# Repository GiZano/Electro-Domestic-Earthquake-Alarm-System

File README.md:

<div align="center">

# 🌋 QuakeGuard
### Distributed Earthquake Early Warning System

**Full-Stack IoT Architecture for Real-Time Earthquake Detection**

> 📚 **Technical Specification:** A comprehensive architecture whitepaper is available in the `docs/` directory, compiled via Typst. For a browsable, topic-by-topic reference, check out the [project Wiki](https://github.com/GiZano/QuakeGuard/wiki).

</div>

---

🌐 **[Landing Page](https://giovanni-zanotti.is-a.dev/projects/quakeguard.html)** · 📚 **[Wiki](https://github.com/GiZano/QuakeGuard/wiki)** · 📄 **[Whitepaper (PDF)](docs/whitepaper/)** · 🗺️ **[ROADMAP](ROADMAP.md)**

---

## 📖 Overview

**QuakeGuard** is a full-stack IoT architecture for real-time detection, analysis, and reporting of seismic events. The system transforms everyday household appliances — washing machines, TVs, refrigerators — into a distributed seismic sensor network, each node capable of detecting and reporting earthquake activity autonomously.

Intelligent edge sensors (ESP32-C3 + ADXL345) analyze vibrations locally using professional-grade algorithms and transmit cryptographically signed data to an asynchronous cloud backend. The backend is engineesred to handle the massive traffic spikes — the **Thundering Herd** effect — typical during widespread seismic events, ensuring reliable alarm delivery without bottlenecking. A React Native mobile app receives real-time haptic and visual alerts via WebSocket.

### QuakeGuard Proprietary Hardware

*The QuakeGuard v2.0 fully assembled PCB, featuring the ESP32-C3 SuperMini, the ADXL345 accelerometer, and the u-blox GNSS module. For a complete list of required components, refer to the [Bill of Materials (BOM)](https://github.com/GiZano/QuakeGuard/wiki/Bill-of-Materials) in the Wiki.*

---

## 🏗️ System Architecture

```
ESP32-C3 + ADXL345
       │
       │  MQTT (signed payload)
       ▼
MQTT Bridge ──► POST /readings/ ──► ECDSA Verification
                                              │
                                              ▼
                                        Redis Queue
                                              │
                                              ▼
                                     Background Worker ────►┌───────────┐
                                      │           │ (Queue)  │ AI Worker │
                                      ▼           ▼          │ (Ollama)  │
                               PostgreSQL    Redis Pub/Sub ◄─└─────┬─────┘
                               + PostGIS               │
                                                   ▼
                                            WebSocket Broadcast
                                                  │
                                                  ▼
                                        React Native Mobile App
                                        (Haptic + Visual Alert)
```

The project follows **Microservices** and **Event-Driven Design** principles across three fully independent layers.

---

## 📡 IoT Edge (`firmware/`)

| Feature | Detail |
|---------|--------|
| Hardware | ESP32-C3 SuperMini + ADXL345 Accelerometer |
| Sampling Rate | 100 Hz |
| Detection Algorithm | STA/LTA (Short Term / Long Term Average) |
| Signal Processing | Digital High-Pass Filter (HPF) to remove gravity |
| Data Structure | Statically allocated Ring Buffers (`RingBuffer<100>` STA, `RingBuffer<1000>` LTA) |
| Security | ECDSA NIST256p cryptographic signing on every payload |
| Transmission | MQTT publish to `quakeguard/telemetry` |
| Provisioning | Automated device handshake on first boot via `POST /devices/register` |
| Secret Injection | Compile-time `ENROLLMENT_TOKEN` via PlatformIO pre-script + `#error` fail-fast |

---

## ☁️ Backend (`backend/`)

| Feature | Detail |
|---------|--------|
| Framework | FastAPI (Python 3.11), fully async |
| Security | API Key auth, ECDSA signature verification, Anti-Replay (300s window) |
| Message Broker | Redis — decouples ingestion from processing |
| Rate Limiting | Fixed-window 50 req/s per IP via Redis |
| Alert Engine | ML-like magnitude proxy (`M = log10(PGA_calib) + b`), threshold M ≥ 4.5 |
| Deduplication | Redis TTL cooldown lock per zone (60s), prevents alert storms |
| Persistence | PostgreSQL + PostGIS with `recorded_at` timestamps |
| Zone Assignment | Automatic via PostGIS `ST_Contains` spatial query, ordered by `ST_Area` ascending |
| Zone Seeding | 8 pre-populated global macro-regions + "Unknown Region" fallback |
| Observability | `GET /health` — concurrent PostgreSQL + Redis ping |
| Secrets | Fail-fast `RuntimeError` on missing env vars at startup |
| MQTT Bridge | `mqtt_subscriber.py` — forwards MQTT payloads to the secure HTTP pipeline |
| Edge AI | Asynchronous emergency report generation via local Ollama (Llama 3.2) |

---

## 📱 Frontend (`mobile/`)

| Feature | Detail |
|---------|--------|
| Framework | React Native (Expo) with TypeScript |
| Navigation | Expo Router — 3-tab Bottom Navigator (Monitor, Sensors Map, Settings) |
| State Management | Zustand slices (`usePreferencesStore`, `useAlertStore`) |
| Server State | TanStack Query + Axios — caching, background refetch, retry |
| Real-Time | WebSocket context with exponential backoff reconnection |
| Alert Delivery | SOS haptic vibration pattern + OS push notification via `expo-notifications` |
| Alert History | In-session feed of last 10 critical events |
| AI Report Banner | Inline AI-generated emergency report (summary + recommendations) for the latest alert, with "Report unavailable" badge on failures |
| Offline Mode | Toggle silences WebSocket, halts all TanStack Query polling |
| Notifications | `notificationsEnabled` toggle gates haptics and push notifications |
| Safe Areas | `react-native-safe-area-context` — Dynamic Island and punch-hole compatible |

---

## 🔐 Security Model

Data integrity is paramount in an emergency system. Every telemetry packet is cryptographically secured end-to-end.

```
ESP32 signs payload with ECDSA NIST256p (SHA256)
         ↓
Backend verifies signature against registered public key
         ↓
Timestamp validated within 300-second window (Anti-Replay)
         ↓
API Key checked on every request (X-API-Key header)
         ↓
Payload accepted → Redis Queue
```

**Threat model coverage:**
- ✅ Man-in-the-Middle (MitM) — ECDSA signature verification
- ✅ Spoofing — public key registration + signature check
- ✅ Replay attacks — 300-second timestamp window
- ✅ Brute force — rate limiting 50 req/s per IP
- ✅ Unauthorized access — API Key + enrollment token fail-fast

---

## 🚀 Quick Start

### Prerequisites

- Docker Desktop & Docker Compose
- PlatformIO (VS Code Extension)
- Node.js 18+ & Expo Go (mobile)
- A mobile hotspot or shared WiFi network for ESP32 + backend connectivity

### 1. Configure Environment Variables

```bash
cd backend
cp .env.example .env
```

Edit `.env` and set the required secrets:

```env
# --- Application Secrets ---
IOT_API_KEY=your_secret_key
MOBILE_WS_TOKEN=your_ws_token
ENROLLMENT_TOKEN=your_enrollment_token

# --- Database ---
POSTGRES_DB=quakeguard_db
POSTGRES_USER=developer
POSTGRES_PASSWORD=your_db_password
API_PORT=8000

# --- Cloud MQTT (HiveMQ) ---
MQTT_BROKER=your-cluster-id.s1.eu.hivemq.cloud
MQTT_PORT=8883
MQTT_USERNAME=your_mqtt_username
MQTT_PASSWORD=your_mqtt_password

# --- AI Emergency Reports (hybrid Edge AI architecture) ---
AI_REPORT_ENABLED=true
OLLAMA_HOST=http://127.0.0.1:11434
OLLAMA_MODEL=llama3.2:1b
```

> ⚠️ The backend will refuse to start if any of these are missing — this is intentional fail-fast behavior.

> 💡 **Edge AI Architecture (v2.0.0):** To maximize hardware efficiency and avoid Docker's GPU passthrough overhead, QuakeGuard employs an industrial **Hybrid Edge AI** pattern (similar to NVIDIA Jetson or Tesla FSD architectures). The core AI inference engine (Ollama) runs bare-metal on the host Linux OS, while the application microservices run in Docker and communicate via `network_mode: "host"`.
> 
> **To enable on-premise AI reports:**
> 1. Install Ollama natively on your Linux host: `curl -fsSL https://ollama.com/install.sh | sh`
> 2. Pull the model natively: `ollama pull llama3.2:1b`
> 3. Start the Docker stack with the AI worker profile: `docker compose --profile ai up --build -d`
> 
> Reports are generated entirely on your machine: telemetry never leaves the host.

### 2. Launch the Backend Stack

```bash
cd backend
docker compose up --build -d
```

| Endpoint | URL |
|----------|-----|
| API | `http://localhost:8000` |
| Swagger UI | `http://localhost:8000/docs` |
| Health Check | `http://localhost:8000/health` |

### 3. Configure and Flash the IoT Firmware

```bash
cd firmware
cp esp32_config.env.example esp32_config.env
# Edit esp32_config.env with your network IP and ENROLLMENT_TOKEN
```

Flash via PlatformIO. On first boot the device will:
1. Open a WiFi captive portal (`QuakeGuard-Setup`)
2. Connect to your network
3. Automatically register with the backend and receive a `sensor_id`

> 💡 If the sensor registers with `latitude=0.0, longitude=0.0` it will be assigned to "Unknown Region". Hardcode your coordinates in `main.cpp` for correct zone assignment until GPS integration is complete.

### 4. Launch the Mobile App

```bash
cd mobile
npm install
```

Update `constants/config.ts` with your machine's local IP:

```typescript
export const API_BASE_URL = "http://YOUR_LOCAL_IP:8000";
```

Create `.env` in the mobile root:

```env
EXPO_PUBLIC_IOT_API_KEY=your_secret_key
EXPO_PUBLIC_MOBILE_WS_TOKEN=your_ws_token
```

```bash
npx expo start
```

Scan the QR code with Expo Go. Ensure your phone is on the **same WiFi network** as the backend machine.

---

## 🧪 Stress Test

Validates the full pipeline: ingestion → Redis → worker → PostGIS → WebSocket alerts.

```bash
cd backend
export API_URL="http://localhost:8000"
export NUM_SENSORS=150
export CONCURRENCY_LIMIT=50
python -m tests.stress_test
```

**Three phases:**

| Phase | What it tests |
|-------|--------------|
| 🔥 Phase 1 — Firehose | 150 concurrent sensors, rate limiter validation |
| ⚔️ Phase 2 — Security | Bad signature blocked (401), Replay attack blocked (403) |
| 🔍 Phase 3 — E2E | DB persistence verified via polling `GET /sensors/{id}/statistics` |

A successful run ends with `🏆 SYSTEM CERTIFIED`.

---

## 🎮 Demo Mode

Trigger a simulated earthquake instantly from Swagger UI without running the stress test:

```
POST /demo/trigger-earthquake
```

Default payload (works with empty `{}`):
```json
{
  "zone_id": 1,
  "magnitude": 7.5,
  "message": "Simulated Critical Event"
}
```

This publishes directly to the Redis `quake_alerts` channel, bypassing the IoT pipeline entirely and triggering the mobile app alert UI within milliseconds.

---

## 🗺️ Geographic Zones

The database is pre-seeded with 8 global macro-regions. Sensors are automatically assigned to the correct zone via PostGIS spatial query at registration time.

| Zone | Coverage |
|------|----------|
| Italy - North | Lombardy, Veneto, Piedmont |
| Italy - Center | Tuscany, Lazio, Umbria |
| Italy - South & Islands | Campania, Sicily, Sardinia |
| Western Europe | France, Spain, Germany, UK |
| North America | USA, Canada, Mexico |
| South America | Brazil, Argentina, Chile |
| East Asia | China, Japan, India |
| Unknown Region | Fallback for unmapped coordinates |

---

## 🔄 CI/CD Pipeline

| Workflow | Trigger | Checks |
|----------|---------|--------|
| `backend-ci.yml` | `backend/**` | Bandit, Safety, stress test |
| `frontend-ci.yml` | `mobile/**` | ESLint, npm audit |
| `iot-ci.yml` | `firmware/**` | PlatformIO compilation |
| `pr-lint.yml` | All PRs | Semantic PR title (`type(scope): message`) |
| `devops-ci.yml` | `.github/workflows/**` | Actionlint workflow validation |

---

## 🗂️ Project Structure

```
QuakeGuard/
├── backend/
│   ├── src/
│   │   ├── main.py              # FastAPI gateway + REST endpoints
│   │   ├── security.py          # ECDSA, API Key, Anti-Replay
│   │   ├── worker.py            # Redis consumer + magnitude + alert engine + AI enqueue
│   │   ├── ai_report_worker.py  # Dedicated AI report consumer (Ollama + state machine)
│   │   ├── ollama_client.py     # Deterministic LLM client (anti-hallucination)
│   │   ├── mqtt_subscriber.py   # MQTT to HTTP bridge
│   │   ├── seed.py              # Geographic zone seeder
│   │   ├── models.py            # SQLAlchemy ORM models (+ EmergencyReport)
│   │   ├── schemas.py           # Pydantic request/response schemas
│   │   └── database.py          # DB engine and session factory
│   ├── tests/
│   │   ├── stress_test.py       # Critical E2E stress test suite
│   │   └── unit/                # Unit tests (worker, ollama client, AI worker, models, ...)
│   ├── init-scripts/
│   │   └── ollama-entrypoint.sh # Auto-pulls the Ollama model on startup
│   ├── build.ps1                # Automatic container publish
│   ├── docker-compose.yml
│   ├── Dockerfile
│   ├── mosquitto.conf
│   ├── requirements.txt         # Python requirements for backend development
│   └── .env.example
├── mobile/
│   ├── app/                         # Expo Router screens
│   │   └── (tabs)/
│   │       ├── index.tsx            # Monitor / Dashboard
│   │       ├── map.tsx              # Sensor Network Map
│   │       └── settings.tsx         # User Preferences
│   ├── api/                         # Axios client + TanStack Query hooks
│   ├── components/                  # Shared UI components
│   ├── store/                       # Zustand state slices
│   ├── context/
│   │   └── WebSocketContext.tsx     # Real-time alert context
│   └── constants/
│       └── config.ts                # Centralized configuration
├── firmware/
│   ├── src/
│   │   ├── main.cpp             # FreeRTOS tasks, STA/LTA, MQTT, provisioning
│   │   ├── DetectionCore.h      # Pure-C++ STA/LTA core (shared firmware/host, R1)
│   │   └── RingBuffer.h         # Statically allocated circular buffer
│   ├── tools/
│   │   └── detect_cli.cpp       # Native host CLI (SIL replay, same core)
│   ├── test/                    # Test scripts to insert into the ESP32
│   ├── key-generator/           # ECDSA key generator for backend testing
│   ├── esp32_config.env.example
│   ├── extra_script.py          # ENV variables injector
│   └── platformio.ini
├── research/                    # SIL validation (ROADMAP R1)
│   ├── fetch_itaca.py           # ITACA download (graceful degradation) / synthetic fallback
│   ├── synthetic.py             # Realistic synthetic dataset generator
│   ├── calibrate_io.py          # Dataset layout I/O + path-injection guard
│   ├── orchestrator.py          # Compile & run the host C++ CLI (subprocess bridge)
│   ├── metrics.py               # Sensitivity, False-Alarm Rate, latency, ROC
│   ├── calibrate.py             # TRIGGER_RATIO x NOISE_FLOOR sweep (F1 maximization)
│   ├── plot_roc.py              # ROC curve figure for the paper
│   ├── requirements.txt         # matplotlib (optional, plotting)
│   └── README.md                # Dataset layout, unit conversion, licensing policy
└── docs/                            # Technical Documentation
    ├── main.typ                     # Typst Whitepaper Entrypoint
    ├── 01-architecture.typ          # System Architecture & Overview
    ├── 02-hardware.typ              # Hardware & Edge Computing (ESP32-C3)
    ├── 03-security.typ              # Cryptographic Security & Provisioning
    ├── 04-broker.typ                # Data Plane & Message Broker (MQTT)
    ├── 05-backend.typ               # Backend Services & Event Processing
    ├── 06-mobile.typ                # Mobile Client & Live Telemetry
    ├── 07-deployment.typ            # Deployment & CI/CD
    └── 08-ai.typ                    # AI Emergency Report Service (v1.2.0)
```

---

## 🔮 Roadmap

| Version | Focus |
|---------|-------|
| **v1.0** | ✅ Released — edge seismic detection on ESP32, local alerts |
| **v1.1** | ✅ Released — HiveMQ Cloud MQTT (TLS), ngrok HTTPS tunnel, security hardening |
| **v1.2** | ✅ Released — On-Premise AI Worker (Local Ollama / Llama 3.2) for privacy-preserving emergency reports |
| **v1.2.1** | ✅ Released — Geo-Zoning & Cooldown Fragmentation — geohash Redis zone index (FastAPI/PostGIS source of truth), per-area cooldown, GNSS-ready data model (`Sensor.last_fix_at`, `Reading.lat/lon`), per-zone live seismograph |
| **v1.2.2** | ✅ Released — Zero-Trust Serial Fallback — signed telemetry over USB CDC (serial) when MQTT is unreachable |
| **v2.0.0** | ✅ Released — Triangulation (multi-node spatial correlation), Hybrid Network Architecture, Automated DevOps Orchestration (Ptyxis), Local Factory Provisioning, GNSS sync, NTP+PPS, ADXL calibration, and INGV FDSN SIL validation |
| **v2.0.1** | ✅ Released — Documentation & Zenodo Sync: PDF/Wiki architectural coherence (Cloudflare, 300s anti-replay), CERN-OHL hardware licensing, SIL vs Firmware threshold clarification, and `CITATION.cff` bump |
| **v2.0.2** | ✅ Released — Repository Health: Dependabot, Gitleaks CI, ADRs, C4/sequence diagrams, multi-stage Dockerfile, firmware versioning, pinout table, flashing guide, privacy policy, hardware compliance disclaimer |
| **v2.1** | Data Dashboards — Grafana dashboards for real-time visualization of seismic telemetry |
| **v2.1.1** | Timeseries DB & Mobile Fix — migration to TimescaleDB/InfluxDB; per-sensor chart isolation in React Native mobile |
| **v2.2** | Heterogeneous Edge Intelligence — hybrid Tier A (STA/LTA) + Tier B (quantized CNN) decision fusion |
| **Future** | Cloud IaC — Kubernetes + Terraform auto-scaling platform (see [ROADMAP.md](ROADMAP.md)) |

### #Research — Scientific Validation (SIL)

| Node | Focus |
|------|-------|
| **#Research** | Parallel ongoing node — SIL cross-validation: replay of the exact production C++ STA/LTA core (`DetectionCore.h`) on the host via the same C++ source, Python-only as orchestrator, ROC metrics + AI benchmarking (latency P50/P99, hallucination rate). R1 pipeline (core isolation, host CLI, orchestrator, metrics, calibration) implemented; see [ROADMAP.md](ROADMAP.md) |

---

## 🏆 Awards & Recognition

QuakeGuard's architecture and real-world applicability have been recognized in the following academic and industrial contexts:

* 🥇 **1st Place Overall - Institute Project Day (2025):** Awarded best technical project out of ~20 prototypes across four engineering disciplines (Computer Science, Automation, Mechanics, Chemistry). The full-stack architecture was evaluated and awarded by an industrial jury featuring technical representatives from **Siemens, ABB, SORINT.lab, SAME, Ferrero, and Confindustria**.
* 🎓 **Academic Origin & Consultation:** The system's conceptualization originated during the 2025 CQIIA-MatNet Summer School (Università di Bergamo). The distributed network logic and spatial deployment strategy were subsequently refined following technical consultations with Prof. F. Finazzi.
* 🏅 **GF Marilli Competition:** [Currently competing - Pending evaluation].

---

## 📄 License

This project is licensed under the **GNU Affero General Public License v3.0 (AGPL-3.0)**.
See the [LICENSE](LICENSE) file for details.

Hardware designs (`hardware/`) are licensed under the **CERN Open Hardware Licence v2 — Strongly Reciprocal (CERN-OHL-S-2.0)**.
See [hardware/LICENSE](hardware/LICENSE) for details.

> ⚠️ **Hardware Compliance:** The QuakeGuard PCB is **not certified for CE/FCC/RoHS**. It is intended for **prototyping, educational, and research use only**. Do not deploy as a commercial safety-critical device without appropriate regulatory certification.

---

<div align="center">

**Developed by [GiZano](https://giovanni-zanotti.is-a.dev) and [riccardo0731](https://riccardo0731.github.io)**
<br>
*Open Source — AGPL-3.0 License*
<br><br>

</div>

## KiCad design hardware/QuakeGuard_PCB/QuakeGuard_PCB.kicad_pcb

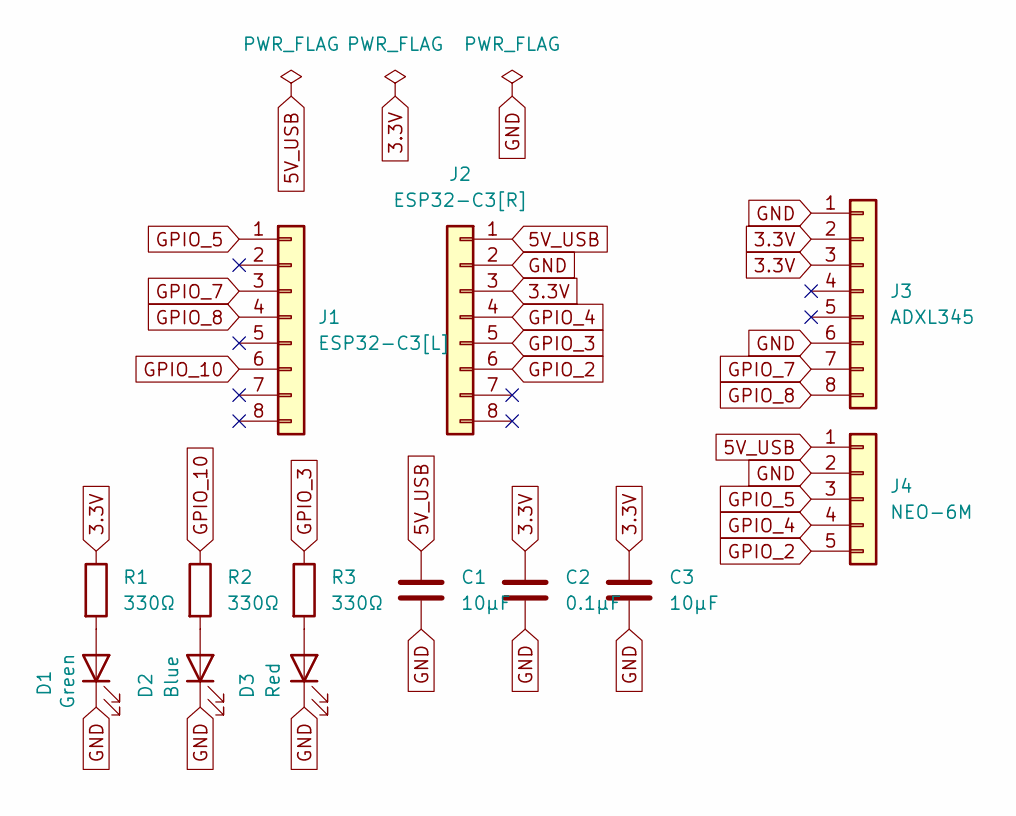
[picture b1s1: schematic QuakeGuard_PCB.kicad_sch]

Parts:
C1, C3: 10µF; CP_Radial_D5.0mm_P2.50mm
C2: 0.1µF; C_Disc_D5.0mm_W2.5mm_P5.00mm
D1: Green; LED_D5.0mm
D2: Blue; LED_D5.0mm
D3: Red; LED_D5.0mm
J1: ESP32-C3[L]; PinSocket_1x08_P2.54mm_Vertical
J2: ESP32-C3[R]; PinSocket_1x08_P2.54mm_Vertical
J3: ADXL345; PinSocket_1x08_P2.54mm_Vertical
J4: NEO-6M; PinSocket_1x05_P2.54mm_Vertical
R1, R2, R3: 330Ω; R_Axial_DIN0207_L6.3mm_D2.5mm_P10.16mm_Horizontal

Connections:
3.3V: C2.1, C3.1, J2.3, J3.2, J3.3, R1.1
5V_USB: C1.1, J2.1, J4.1
GND: C1.2, C2.2, C3.2, D1.1 (K), D2.1 (K), D3.1 (K), J2.2, J3.1, J3.6, J4.2
GPIO_2: J2.6, J4.5
GPIO_3: J2.5, R3.1
GPIO_4: J2.4, J4.4
GPIO_5: J1.1, J4.3
GPIO_7: J1.3, J3.7
GPIO_8: J1.4, J3.8
GPIO_10: J1.6, R2.1
unnamed: D1.2 (A), R1.2
unnamed: D2.2 (A), R2.2
unnamed: D3.2 (A), R3.2

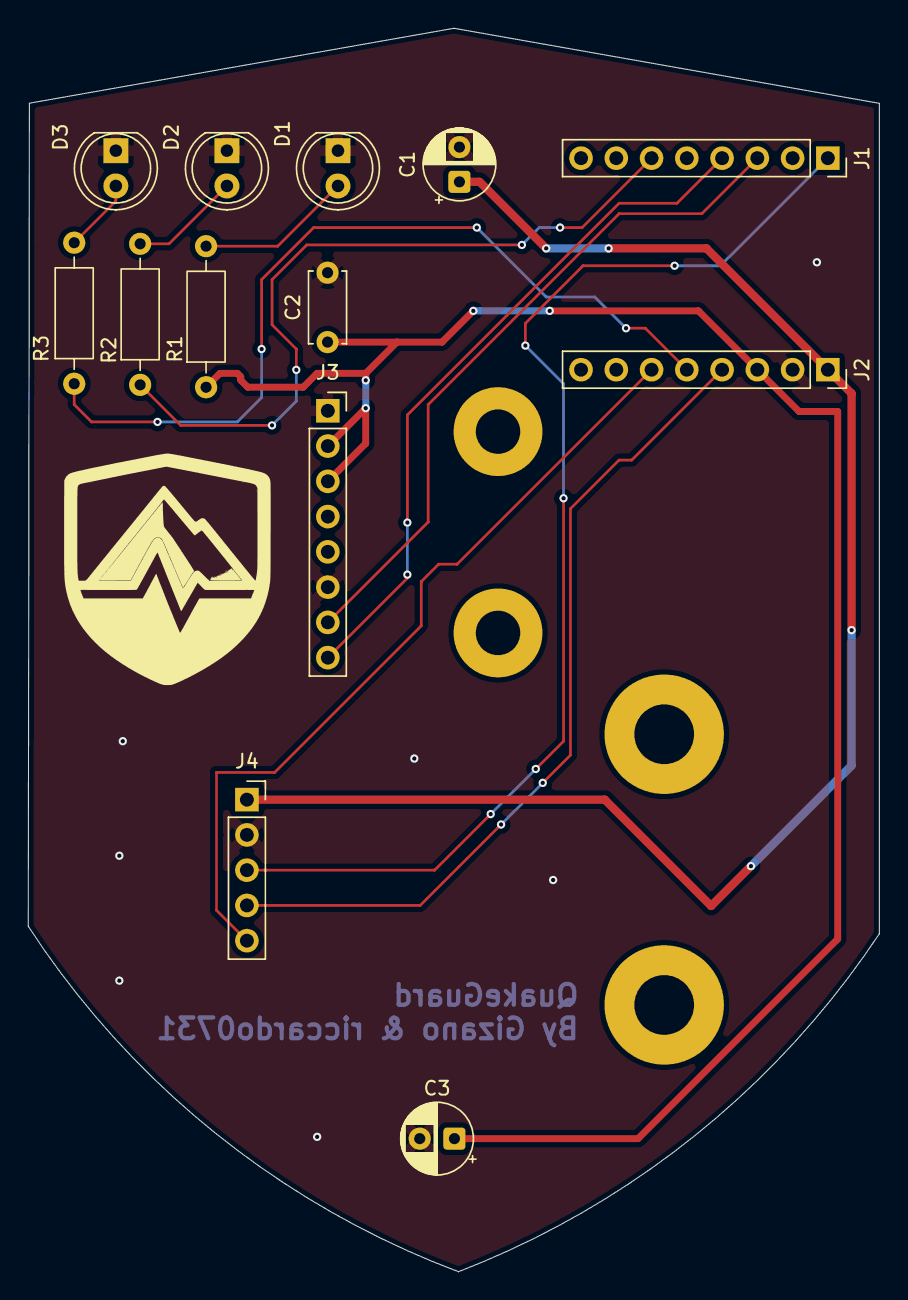
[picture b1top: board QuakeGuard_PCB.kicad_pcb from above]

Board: 2 copper layers, 61.3 x 89.6 mm, 13 parts (0 on the bottom side), 13 nets.

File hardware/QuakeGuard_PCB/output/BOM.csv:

"Refs","Value","Footprint","Qty","DNP"
"C1","10µF","Capacitor_THT:CP_Radial_D5.0mm_P2.50mm","1",""
"C2","0.1µF","Capacitor_THT:C_Disc_D5.0mm_W2.5mm_P5.00mm","1",""
"C3","10µF","Capacitor_THT:CP_Radial_D5.0mm_P2.50mm","1",""
"D1","Green","LED_THT:LED_D5.0mm","1",""
"D2","Blue","LED_THT:LED_D5.0mm","1",""
"D3","Red","LED_THT:LED_D5.0mm","1",""
"J1","ESP32-C3[L]","Connector_PinSocket_2.54mm:PinSocket_1x08_P2.54mm_Vertical","1",""
"J2","ESP32-C3[R]","Connector_PinSocket_2.54mm:PinSocket_1x08_P2.54mm_Vertical","1",""
"J3","ADXL345","Connector_PinSocket_2.54mm:PinSocket_1x08_P2.54mm_Vertical","1",""
"J4","NEO-6M","Connector_PinSocket_2.54mm:PinSocket_1x05_P2.54mm_Vertical","1",""
"R1","330Ω","Resistor_THT:R_Axial_DIN0207_L6.3mm_D2.5mm_P10.16mm_Horizontal","1",""
"R2","330Ω","Resistor_THT:R_Axial_DIN0207_L6.3mm_D2.5mm_P10.16mm_Horizontal","1",""
"R3","330Ω","Resistor_THT:R_Axial_DIN0207_L6.3mm_D2.5mm_P10.16mm_Horizontal","1",""

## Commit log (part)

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2025-11-18 Added empty containerized DB (PostgreSQL) for development
2025-11-19 Working Backend (No alert system, TODO: README.md 's
2025-11-27 Refactor code structure for improved readability and maintainability
2026-04-21 test: enforce strict E2E persistence assertions in stress test
    - Update `verify_persistence_with_polling` to safely select a valid test subject (`sensor_id > 0` and `sent_count > 0`).
    - Implement strict data integrity assertion requiring `total_readings >= sent_count` to guarantee 100% of dispatched payloads were persisted.
    - Ensure semaphore acquisition remains inside the polling loop to strictly respect concurrency limits during E2E verification.
    Closes #68, Closes #69, Closes #70, Closes #71
2026-04-21 feat: implement concurrent infrastructure health check endpoint
    - Add \`GET /health\` endpoint to monitor core backend dependencies.
    - Implement parallel Redis and PostgreSQL connection validation via \`asyncio.gather()\`.
    - Wrap synchronous SQLAlchemy DB pings in \`run_in_executor\` (extracted to module level) to prevent event loop blocking.
    - Add standard stdout logging for intercepted connection exceptions to aid production debugging.
    - Dynamically return \`200 OK\` or \`503 Service Unavailable\` with a detailed JSON status map.
    Closes #53, Closes #74, Closes #75, Closes #76, Closes #77, Closes #78
2026-04-22 fix: api base url for demonstration
2026-04-22 feat: complete mobile navigation structure via Expo Router
    - Update `app/(tabs)/_layout.tsx` to include the third core tab (Settings).
    - Standardize bottom navigation icons using Lucide React Native (`ShieldCheck`, `Map`, `Settings`).
    - Create `app/(tabs)/settings.tsx` interface with functional UI toggles.
    - Wire Settings screen to global Zustand `usePreferencesStore` to handle offline mode and notification preferences.
    Closes #35, Closes #36, Closes #37, Closes #38
2026-04-23 feat: add recorded_at timestamp to Misuration model
    - Add `recorded_at` column to Misuration SQLAlchemy model with UTC `func.now()` default.
    - Update `Misuration` Pydantic response schema to expose the new `recorded_at` field.
    - Remove non-database security fields (`device_timestamp`, `server_timestamp`, `signature_hex`) from the response schema to prevent 500 Internal Server errors during data retrieval.
    Closes #102, Closes #103, Closes #104, Closes #105, Closes #106
2026-04-23 feat: implement automated device provisioning and fail-fast token validation
    - Add `DeviceRegisterRequest` Pydantic schema for the hardware handshake payload.
    - Implement `POST /devices/register` endpoint to validate enrollment tokens, ensure idempotency, and assign DB IDs.
    - Add autonomous fallback logic to create an "Unassigned Provisioning Zone" to prevent foreign key constraint crashes on fresh databases.
    - Implement strict fail-fast startup validation for `ENROLLMENT_TOKEN` via `os.getenv`, removing hardcoded string literals.
    - Pass `ENROLLMENT_TOKEN` to `fastapi-app` in `docker-compose.yml`.
    - Add `.env.example` in order to make it easier to create the configuration file when starting
2026-04-23 ci: revamp CI pipelines with path filtering, IoT build validation, and secure credentials
    - Remove monolithic `quakeguard-ci.yml` to prevent duplicate and noisy pipeline executions.
    - Split CI into `backend-ci.yml`, `frontend-ci.yml`, and `iot-ci.yml` with path-based triggers to drastically reduce wasted CI minutes.
    - Introduce PlatformIO build validation in `iot-ci.yml` to automatically catch C++ syntax and configuration errors.
    - Create `esp32_config.env.example` and inject dummy `ENROLLMENT_TOKEN` to satisfy IoT compile-time `#error` checks.
    - Refactor `backend-ci.yml` to replace hardcoded dummy database credentials with GitHub Actions `${{ secrets.* }}`.
    - Update `pg_isready` readiness c
2026-04-23 ci(core): bump GitHub Actions versions to fix Node 16 deprecation
    - Update `actions/cache` to `v4` to resolve "runner is too old" error.
    - Update `actions/checkout` to `v4` across all workflows.
    - Update `actions/setup-python` to `v5`.
    - Update `actions/setup-node` to `v4`.
    - Ensure all core actions run on supported Node 20 environments.
2026-04-30 feat(backend): replace placeholder magnitude calculation with empirical ML-like proxy
    - Implement MyShake-style PGA conversion formula (M = log10(PGA_calib) + b) in worker.py.
    - Extract calibration constants (K_CALIBRATION, B_OFFSET, SENSOR_SCALE) to environment variables for dynamic tuning.
    - Update Redis alert threshold to trigger on M >= 4.5 instead of raw sensor counts.
    - Modify stress_test.py to occasionally generate high-amplitude values (5000-15000) to accurately simulate M4.5+ events.
    - Fix redundant code in security.py
    Closes #92, Closes #93, Closes #94, Closes #95, Closes #96
2026-04-30 feat(backend): implement atomic Redis TTL cooldown for alert deduplication
    - Implement `alert_cooldown:{zone_id}` distributed lock in `worker.py`.
    - Utilize atomic `SET NX EX` Redis command to prevent TOCTOU race conditions when scaling multiple worker replicas.
    - Add `🚫 ALERT SUPPRESSED` console logging for observability during concurrent trigger events.
    - Upgrade `stress_test.py` with an async Redis Pub/Sub listener to formally verify deduplication (asserting 1 alert per burst).
    Closes #97, Closes #98, Closes #99, Closes #100, Closes #101
2026-04-30 fix(devops): added style scope for frontend style fixes
2026-04-30 fix(devops): added fullstack scope to PR linter
2026-04-30 refactor(frontend): implement shared loading and error UX components
    - Create reusable `<LoadingSkeleton />` and `<ErrorBanner />` in `src/components/`.
    - Refactor `MonitorScreen` (Dashboard) to render shared UI states when TanStack Query is fetching or offline, preventing empty data gaps.
    - Refactor `MapScreen` to utilize shared components for full-screen loading/error states, removing duplicate local implementations.
    - Standardize error messaging to guide users toward connection troubleshooting rather than exposing raw network logs.
    Closes #134, Closes #135, Closes #136, Closes #137, Closes #138
2026-05-01 chore(infra): add Mosquitto MQTT broker to docker-compose
2026-05-01 feat(iot): migrate telemetry transmission from HTTP POST to MQTT publish
2026-05-02 test(core): upgrade stress test for MQTT and fix docker healthcheck
    - Fix Docker healthcheck by replacing with pure-Python to support the base image.
    - Upgrade to v3.0 (MQTT Edition) using for realistic telemetry firehosing.
    - Add End-to-End (E2E) persistence polling and active security attack verification to the stress test.
    - Update files across backend, frontend, and firmware to include realistic mock data and ngrok static domain configurations.
2026-05-08 fix(mqtt): resolve Bandit security warnings in subscriber
2026-05-09 fix(backend): resolve pipeline failure caused by safety vulnerability scanner
2026-05-09 fix(backend): added iot_api_key env to backend-ci
2026-05-09 fix(backend): fixed stress_test crypto libs
2026-05-17 fix(backend): fixed GitHub Actions
2026-05-19 feat(frontend): wire user preferences to expo push notifications and haptics
    Integrated expo-notifications and expo-device to handle OS-level
    alert banners and hardware vibrations. Gated all Vibration.vibrate()
    and scheduleNotificationAsync() calls behind the Zustand
    notificationsEnabled toggle to ensure the app respects user muting.
    Closes #123
2026-05-19 fix(frontend): wire offline mode to network transport layers
    Tied the Zustand isOfflineMode toggle directly to the WebSocket
    connection and TanStack Query hooks. The WebSocket now closes
    gracefully and all HTTP polling pauses when offline mode is active,
    preventing background network errors and saving battery.
    Closes #129
2026-05-19 fix(frontend): wire offline mode to network transport layers (#280)
    * fix(frontend): wire offline mode to network transport layers
    Tied the Zustand isOfflineMode toggle directly to the WebSocket
    connection and TanStack Query hooks. The WebSocket now closes
    gracefully and all HTTP polling pauses when offline mode is active,
    preventing background network errors and saving battery.
    Closes #129
2026-05-19 feat(backend): add demo endpoint to trigger simulated alerts (#281)
    Added a secure POST /demo/trigger-earthquake endpoint to main.py.
    It bypasses the IoT ingestion worker and publishes a crafted
    CRITICAL payload directly to the Redis Pub/Sub channel, enabling
    instant, reproducible frontend testing and live demonstrations.
    Closes #191
2026-05-19 fix(core): final cleanup pre release
2026-05-20 refactor(core): rename top-level directories for clarity
    - backend-data-elaborator to backend
    - frontend-mobile-app to frontend
    - iot-data-harvester to firmware
2026-06-28 fix(ci): resolve IoT test build, npm audit, and safety scan failures
    - IoT test_native: add test_build_project_src=false to exclude Arduino.h
    - Frontend npm audit: add continue-on-error for pre-existing vulns
    - Backend safety scan: add continue-on-error for pre-existing vulns
    - Backend deps: update aiohttp, idna, starlette, urllib3 to secure versions
2026-06-28 fix(ci): resolve Jest jest-expo incompatibility and PlatformIO test build
    Frontend:
    - Remove jest-expo@52 (incompatible with expo SDK 54)
    - Use ts-jest with node test environment instead
    - Mock react-native, expo-notifications, expo-device via moduleNameMapper
    IoT:
    - Remove PlatformIO test_native environment (incompatible with native build)
2026-06-28 fix(ci): correct Frontend Jest runtime, ESLint and IoT detection threshold
    Frontend:
    - Convert __mocks__/react-native.js from ESM to CJS (Jest runtime
    does not transform .js files, causing 'Unexpected token export')
    - Mock ../constants/config in api.test.ts and quakeStore.test.ts
    (API_BASE_URL was undefined without EXPO_PUBLIC_ env vars)
    - Suppress import/first ESLint warnings for jest.mock hoisting pattern
2026-06-28 chore: update .gitignore, lockfile, and pre-existing mobile fixes
    .gitignore: add *.pdf and node_modules/
    package-lock.json: sync after jest-expo removal and ts-jest addition
    index.tsx: remove unused VictoryAxis import, add ScrollView
    WebSocketContext.tsx: prevent duplicate WebSocket connections
    Also adds monospace() helper for Typst PDF generation
2026-06-29 fix(backend): move wait_for_db() and create_all() into lifespan for async startup (P1.1.1)
2026-06-29 fix(backend): add minimum length validation for env vars (P1.1.2)
2026-06-29 fix(backend): use asyncpg for async health check instead of thread executor (P1.1.3)
2026-06-29 fix(backend): replace SessionLocal() context manager with explicit try/finally (P1.1.4)
2026-06-29 refactor(core): rename Misurator/Misuration to Sensor/Reading across all layers (P1.1.5)
2026-06-29 fix(backend): use X-Forwarded-For header for proxy-aware rate limiting (P1.1.6)
2026-06-29 fix(backend): replace fixed-window rate limiter with sliding window (P1.1.7)
2026-06-29 fix(backend): guard resolve_zone against null coordinates (P1.1.8)
2026-06-29 refactor(backend): extract _create_sensor helper to deduplicate sensor registration (P1.1.9)
2026-06-29 fix(backend): add robust pagination with cap and negative skip guard (P1.1.10)
2026-06-29 fix(backend): use hmac.compare_digest for constant-time API key comparison (P1.2.1)
2026-06-29 fix(backend): use hmac.compare_digest for constant-time API key comparison (P1.2.1) (#293)

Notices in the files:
README.md:
License: AGPL-3.0
